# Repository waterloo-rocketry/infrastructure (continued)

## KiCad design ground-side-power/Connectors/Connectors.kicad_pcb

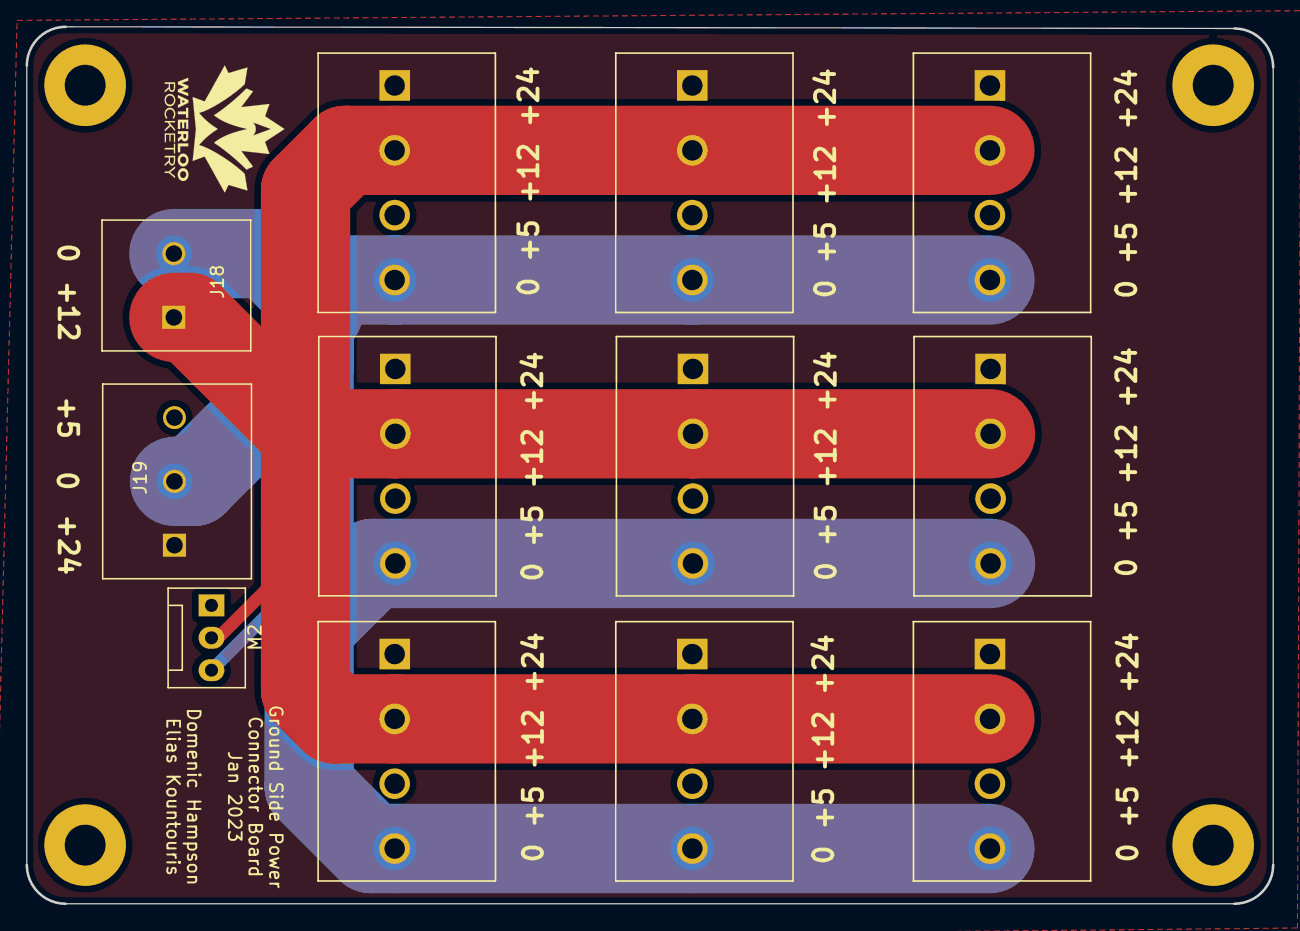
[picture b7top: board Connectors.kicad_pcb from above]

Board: 2 copper layers, 97.7 x 68.7 mm, 12 parts (0 on the bottom side), 4 nets.

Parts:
J15: To Router; CUI_TB008A-508-04BE
J16: To RLCS; CUI_TB008A-508-04BE
J17: To DAQ Laptop; CUI_TB008A-508-04BE
J18: Conn_01x02_Female; 1935310
J19: Conn_01x02_Female; 1935323
J20: To Ethernet; CUI_TB008A-508-04BE
J21: To 5V M12; CUI_TB008A-508-04BE
J22: To DAQ; CUI_TB008A-508-04BE
J23, J24, J25: Extra M12; CUI_TB008A-508-04BE
M2: Fan_PC_Chassis; FanPinHeader_1x03_P2.54mm_Vertical

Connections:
+5V: J15.3, J16.3, J17.3, J19.3, J20.3, J21.3, J22.3, J23.3, J24.3, J25.3
+12V: J15.2, J16.2, J17.2, J18.1, J20.2, J21.2, J22.2, J23.2, J24.2, J25.2, M2.2 (+)
+24V: J15.1, J16.1, J17.1, J19.1, J20.1, J21.1, J22.1, J23.1, J24.1, J25.1
GND: J15.4, J16.4, J17.4, J18.2, J19.2, J20.4, J21.4, J22.4, J23.4, J24.4, J25.4, M2.3 (-)

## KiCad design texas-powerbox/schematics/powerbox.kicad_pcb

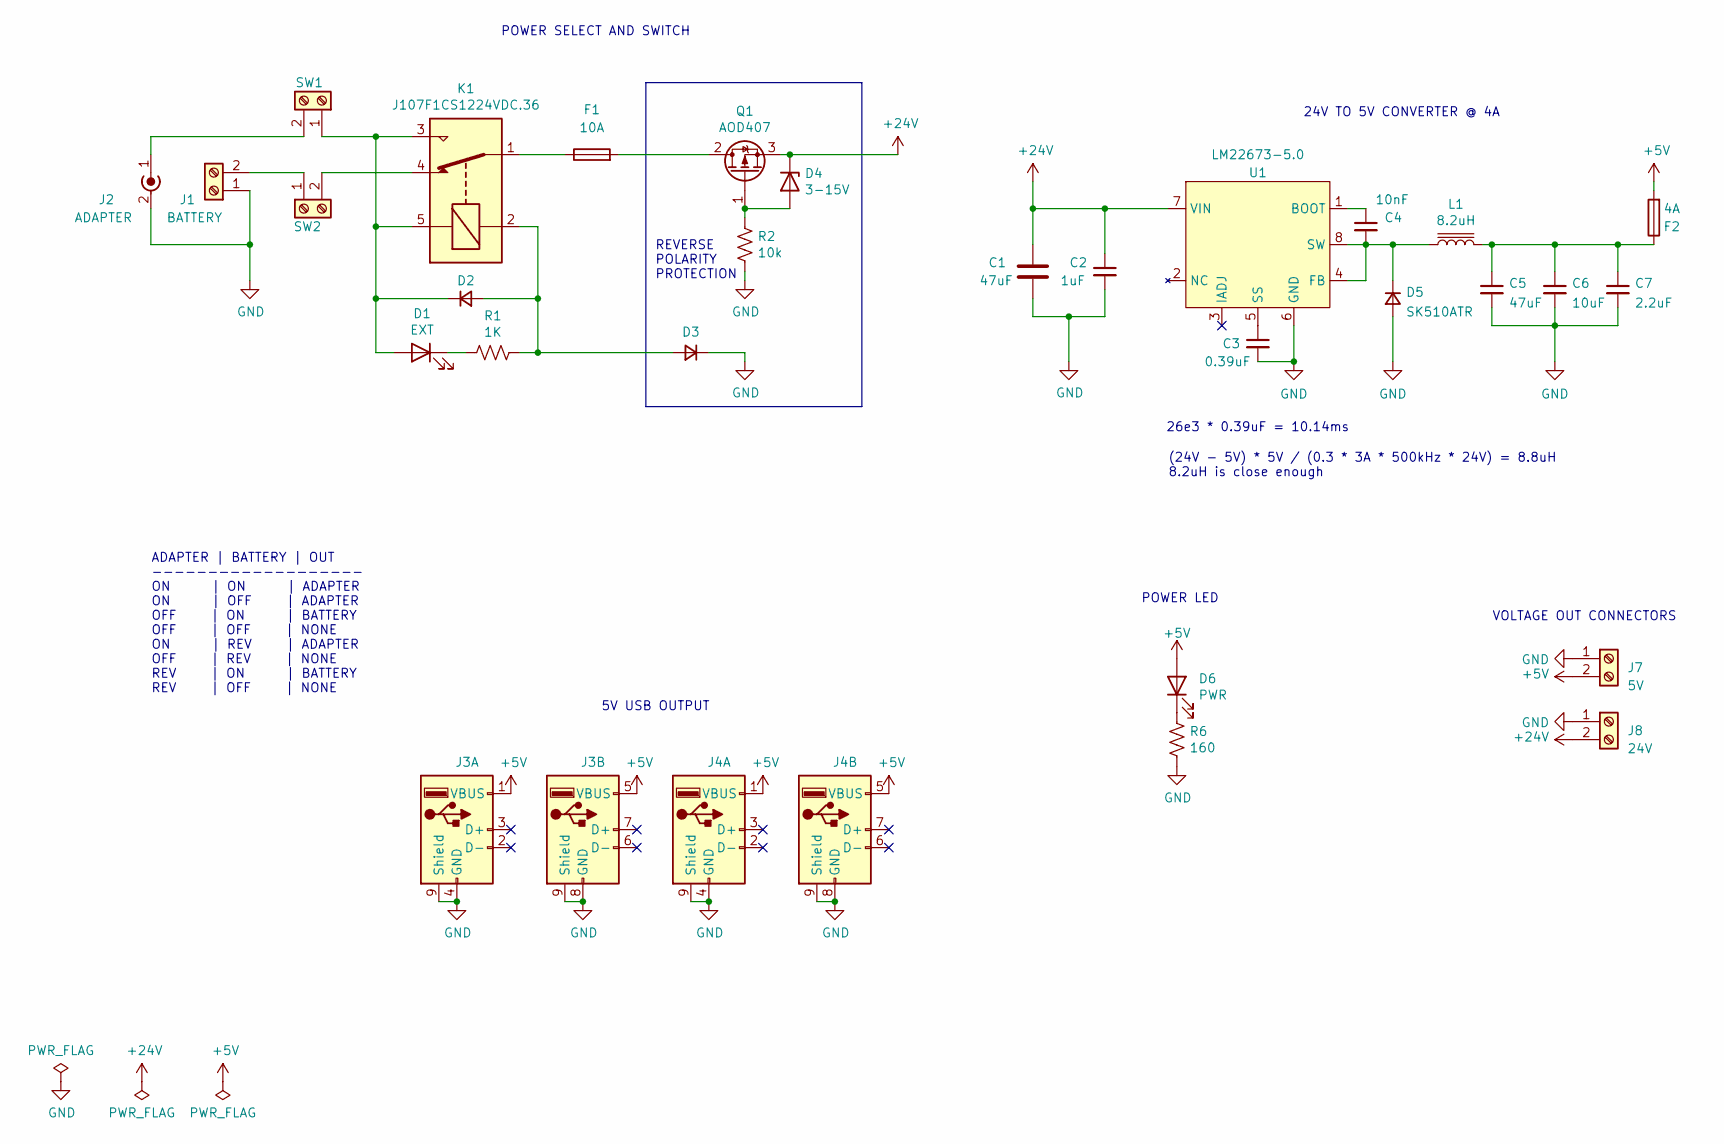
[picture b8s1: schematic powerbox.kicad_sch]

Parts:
C1, C5: 47uF; C_0805_2012Metric_Pad1.18x1.45mm_HandSolder
C2: 1uF; C_0805_2012Metric_Pad1.18x1.45mm_HandSolder
C3: 0.39uF; C_0805_2012Metric_Pad1.18x1.45mm_HandSolder
C4: 10nF; C_0805_2012Metric_Pad1.18x1.45mm_HandSolder
C6: 10uF; C_0805_2012Metric_Pad1.18x1.45mm_HandSolder
C7: 2.2uF; C_0805_2012Metric_Pad1.18x1.45mm_HandSolder
D1: EXT; LED_1206_3216Metric_Pad1.42x1.75mm_HandSolder
D2, D3: BAS19LT3G; D_SOT-23_ANK
D4: 3-15V; D_SOD-123
D5: SK510ATR; D_SMA_Handsoldering
D6: PWR; LED_1206_3216Metric_Pad1.42x1.75mm_HandSolder
F1: 10A; Fuseholder_36-3557-15-ND
F2: 4A; Fuseholder_36-3557-15-ND
J1: BATTERY; BarrierBlock_ED2945-ND
J2: ADAPTER; TENSILITY_54-00167
J3, J4: USB_STACKED; USB_A_Wuerth_61400826021_Horizontal_Stacked
J7: 5V; BarrierBlock_ED2945-ND
J8: 24V; BarrierBlock_ED2945-ND
K1: J107F1CS1224VDC.36; Relay_SPDT_Omron-G5LE-1
L1: 8.2uH; IND_PA4343.103NLT
Q1: AOD407; TO-252-3
R1: 1K; R_0805_2012Metric_Pad1.20x1.40mm_HandSolder
R2: 10k; R_0805_2012Metric_Pad1.20x1.40mm_HandSolder
R6: 160; R_0805_2012Metric_Pad1.20x1.40mm_HandSolder
SW1, SW2: BarrierBlock_ED2945-ND
U1: LM22673-5.0; TI_SO-PowerPAD-8_ThermalVias

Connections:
+5V: D6.2 (A), F2.2, J3.1 (VBUS), J3.5 (VBUS), J4.1 (VBUS), J4.5 (VBUS), J7.2
+24V: C1.1, C2.1, D4.1 (K), J8.2, Q1.3 (S), U1.7 (VIN)
GND: C1.2, C2.2, C3.2, C5.2, C6.2, C7.2, D3.1 (K), D5.2 (A), J1.1, J2.2 (Ext), J3.4 (GND), J3.8 (GND), J3.9 (Shield), J4.4 (GND), J4.8 (GND), J4.9 (Shield), J7.1, J8.1, R2.2, R6.2, U1.6 (GND), U1.9
unnamed: C3.1, U1.5 (SS)
unnamed: C4.1, U1.1 (BOOT)
unnamed: C4.2, D5.1 (K), L1.1, U1.4 (FB), U1.8 (SW)
unnamed: C5.1, C6.1, C7.1, F2.1, L1.2
unnamed: D1.1 (K), R1.2
unnamed: D1.2 (A), D2.1 (K), K1.3, K1.5, SW1.1
unnamed: D2.2 (A), D3.2 (A), K1.2, R1.1
unnamed: D4.2 (A), Q1.1 (G), R2.1
unnamed: D6.1 (K), R6.1
unnamed: F1.1, K1.1
unnamed: F1.2, Q1.2 (D)
unnamed: J1.2, SW2.1
unnamed: J2.1 (In), SW1.2
unnamed: K1.4, SW2.2

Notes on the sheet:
24V TO 5V CONVERTER @ 4A
POWER SELECT AND SWITCH
5V USB OUTPUT
VOLTAGE OUT CONNECTORS
REVERSE POLARITY PROTECTION
26e3 * 0.39uF = 10.14ms
ADAPTER | BATTERY | OUT ------------------- ON | ON | ADAPTER ON | OFF | ADAPTER OFF | ON | BATTERY OFF | OFF | NONE ON | REV | ADAPTER OFF | REV | NONE REV | ON | BATTERY REV | OFF | NONE
(24V - 5V) * 5V / (0.3 * 3A * 500kHz * 24V) = 8.8uH 8.2uH is close enough
POWER LED

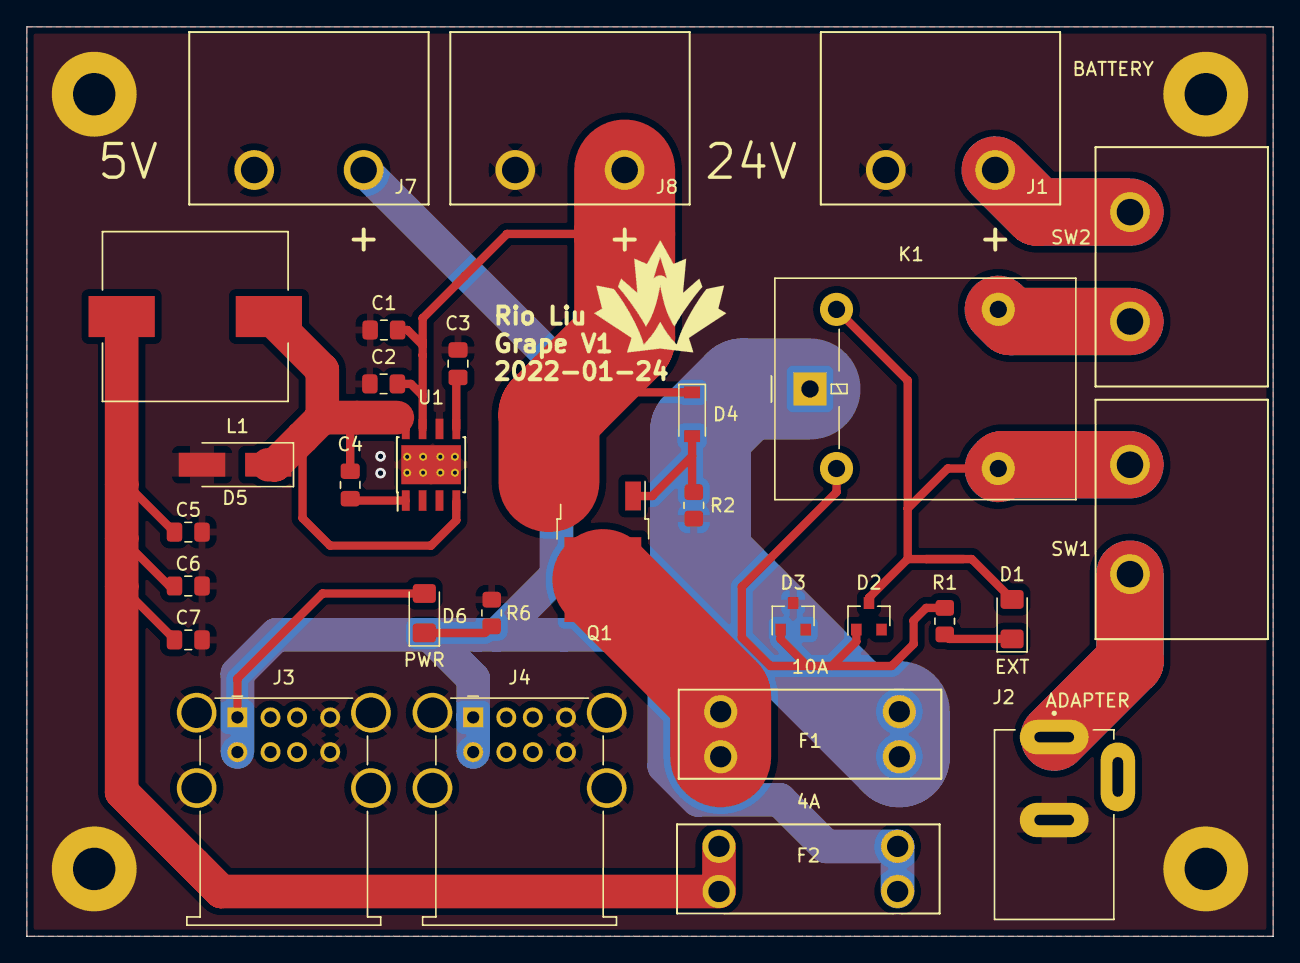
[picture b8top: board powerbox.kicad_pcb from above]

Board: 2 copper layers, 94.0 x 68.6 mm, 30 parts (0 on the bottom side), 17 nets.

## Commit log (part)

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2021-11-30 texas powerbox kicad files
2021-12-02 fix most of the PR issues
2021-12-07 switch to diode based input selection, plus wip 5v regulation
2021-12-08 complete dc-dc converter design
2021-12-09 add power leds and re-layout input select circuit
2021-12-11 replace mosfets in power selection circuit with relay
2021-12-11 fix pr issue
2021-12-11 use mosfet instead of diode for main reverse polarity protection
2021-12-11 put main fuse to ground side and add some comments
2022-01-04 change to high side switching and add voltmeter
2022-01-08 Add footprint for most parts
2022-01-09 Use multiple switching point to achieve high side switching
    so the ground potential doesn't change when switching between supplies
2022-01-09 Update powerbox footprints
2022-01-16 layout
2022-01-16 routing
2022-01-17 Fix pr issues and add logo
2022-01-22 align mounting holes and name the board
2022-01-24 project cleanup
2022-01-25 updated to use alternative bulk converter
2022-01-27 update regulator input capacitor and add comment
2022-01-27 add gerbers
2022-01-27 ground the bulk converter better and updater gerbers
2022-01-27 add polarity silkscreen and update gerbers
2022-11-09 Added GSP Schematics
2022-11-15 Addressed a few comments and added notes to schematic
2022-11-16 Adressed common concerns
2022-11-16 Added refrence designators
2022-11-16 Added Datasheets
2022-11-21 Polarity Protection
2022-12-02 Addressed some comments, will continue working on it tomorrow
2022-12-02 Added Relay + Minor Changes
2022-12-02 Added Datasheet Links
2022-12-03 Added Screw Terminals for M12 connectors and switches
2022-12-04 Added Current and Voltage Sensing for DAQ
2022-12-08 Addressed comments
2022-12-11 Added correct PSU connector
2022-12-22 Changes to Shunt Current Sensors
2022-12-22 Addressed remaining comments
2022-12-23 Changed PSU
2023-01-07 Resolved Remaining Schematic Issues
2023-01-08 Added Footprints
2023-01-11 Fixed footprints
2023-01-12 Split into multiple boards
2023-01-12 Created layout for the footprints for each board
2023-01-13 Added Fan Headers + Thermistor
2023-01-16 PCB Layout First Draft
2023-01-20 Address Input and Converter Comments
2023-01-21 Resolved Final Issues
2023-01-25 Silkscreen and current sense changes
2023-01-26 Small Changes
2023-01-27 Fixed footprint issue
2023-01-27 Fixed footprint error
2023-01-27 Added Gerbers
2023-04-08 resolved issues from testing
2023-05-10 Updated Fuses
2023-11-27 Updated schematic to have matching fuse values
2023-12-14 Update GSPD Board.kicad_sch
    Added new boost converter
2023-12-28 new converter board
2023-12-31 schematic for new converter
2024-01-01 undeleted 5v regulator
2024-01-12 implemented comments
2024-01-13 updatad symbols with correct values
2024-01-30 Created layout
2024-02-06 sourced vertical screw terminals
2024-02-11 completly redid layout
2024-02-14 updates to Input GSPD including AC/DC Autoswitching
2024-03-02 added inductor footprint
2024-03-10 implemented changes
2024-03-10 Updated Input.kicad_pro and added Input.kicad_sch
2024-03-20 New changes from Review
2024-04-05 stitched 5v line
2024-04-15 fixed drc errors and changed thermistor symbol
2024-04-15 removed daisychaining
2024-04-15 generated gerbers and sch pdf
2024-04-16 add pours near boost converter and new gerbers
2024-04-16 connected 5v traces
2024-05-11 corrected vout silkscreen
2024-05-14 rotated component silkscreens to make them parallel to components
2024-05-22 add design for tank heater PCB
2024-06-07 Added adhesive fill on back side of PCB
2024-06-07 Rounded corners
2024-06-10 Add silkscreen, make minor connector position adjustments, and export gerber files
2024-06-12 GSPD Converter Board Respin (#11)
    * schematic for new converter
    * undeleted 5v regulator
    * implemented comments
    * updatad symbols with correct values
    * added footprints
    * Created layout
2024-06-12 Add design for tank heater PCB (#14)
    * add design for tank heater PCB
    * Added adhesive fill on back side of PCB
    * Rounded corners
    * Add silkscreen, make minor connector position adjustments, and export gerber files
    ---------
2024-11-22 12V - 48V DC/DC converter schematic
2024-11-27 Implemented feedback from request
2024-11-27 Changed small text on boost board to make link more accessible
2024-11-27 Added footprint for inrush current limiter
2024-11-29 Changed mosfet symbol to be more accurate to proposed mosfet
2025-01-14 Implemented feedback from request V2
2025-01-14 Implemented feedback from review V3
2025-01-17 First attempt in the pcb layout and routing
2025-01-23 Made all the changes, still working on the refining the track sizes
2025-02-07 Made some changes to track sizes
2025-02-07 Made some schematic and labelling changes, going to probably revamp the entire layout cause I'm pretty unhappy with it and now see the recommended one from the datasheet
2025-03-01 initial schematic for groundside board to supply rocketside charge line current
2025-03-03 Squeezed board closer and rerouted traces
2025-03-19 Fixed tracing issues
2025-03-19 Minor touchup
2025-04-22 Updated as review, let me know if I should just redo the layout completely cause its still a bit scuffed imo
2025-04-23 Made big changes to the layout
2025-04-23 Fixed an edge cut that was locked
2025-05-06 Added mounting holes
2025-05-08 more changes
2025-05-08 reannotated
2025-05-08 remove .lck
2025-05-09 layout and routing
2025-05-09 add kicad footprints submodule
2025-05-10 i would never commit a .lck file guys i swear
2025-05-13 address tessa feedback
2025-05-15 Created car-battery-reverse-polarity-protection project.
    For high current reverse polarity protection for EGSE and tank heating.
2025-05-16 generate gerbs, pdf
2025-05-16 zipped gerbs
2025-05-16 Changed layout to make it more compact, changed output and input cap sizes
2025-05-16 add kicad footprints submodule (#17)
2025-05-19 Made the two resistors bigger, will implement other changes after some discussion
2025-05-21 PCB layout nearly complete.
2025-05-21 PCB layout rev 1 complete.
2025-05-21 Updated silkscreen.
2025-05-25 some WIP changes to the schematic
2025-05-25 Added opamp
2025-05-25 change CC source to CC/CV battery charge IC
2025-05-26 select components and layout/route
2025-05-26 generate gerbs and pdf
2025-05-26 oops.
2025-05-26 remove old gerbs
2025-05-28 Changed silkscreen and vias
2025-05-31 pcb layout
2025-05-31 Changed 63nF cap footprint
2025-05-31 Updated INA290 symbol and footprint
2025-05-31 Actually updated INA290 footprint
2025-05-31 Fixed the second fuse hold to be a holder
2025-06-02 fix silkscreens
2025-06-02 Create groundside charging board (#16)
    * initial schematic for groundside board to supply rocketside charge line current
    * more changes
    * reannotated
    * remove .lck
    * layout and routing
    * i would never commit a .lck file guys i swear
2025-06-03 Update gitignore.
    Removed all .lck files
2025-06-03 PCB and schematic changes:
    - Made board and power traces bigger to meet current requirements.
    - Standardized silkscreen labels.
    - Updated component values in schematic.
2025-06-03 Fixed some small stuff
2025-06-03 Revert connector changes
2025-06-04 Added second op-amp, need to add 5 volt input
2025-06-08 Updates RE: PR
    - Updated diode and relay part numbers.
    - Updated relay symbol.
    Size of board dictated by mounting hole requirement:
    - x distance between holes 37mm
    - y distance 65 mm
2025-06-08 Generated gerbers and schematic PDF.
2025-06-08 Schematic and PCB changes. See descp.
    - Added 12V to 5V LDO to schematic and PCB.
    - Via stitched large planes both due to thermal and GND return path concerns.
    - Other minor tweaks.
2025-06-08 Updated routing and component placement to optimize ground return.
    Next: move input 5V LDO and omp amp to top layer in order not to obstruct gnd path.
2025-06-08 PCB changes. See descp.
    - Moved input current sense and 5V LDO in order not to obstruct GND return.
    - Fixed silkscreen.
    - Adjusted plane connections, plane sizes and thermal reliefs.
    Ready for final review.
2025-06-09 Moved current sense amps. Other minor changes.
2025-06-09 Updated PCB size/mounting hole locations. Moved components around a little.
2025-06-09 Generated gerbers.
2025-06-10 Car battery reverse polarity protection (#18)
    * Created car-battery-reverse-polarity-protection project.
    For high current reverse polarity protection for EGSE and tank heating.
    * PCB layout nearly complete.
    * PCB layout rev 1 complete.
    * Updated silkscreen.
    * Update gitignore.
2025-06-10 New 48V boost board (#15)
    * 12V - 48V DC/DC converter schematic
    * Implemented feedback from request
    * Changed small text on boost board to make link more accessible
    * Added footprint for inrush current limiter
    * Changed mosfet symbol to be more accurate to proposed mosfet
    * Implemented feedback from request V2
